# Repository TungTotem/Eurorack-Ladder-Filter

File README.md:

# Eurorack-Ladder-Filter
PCB and EAGLE files for a simple ladder filter I found on the internet. 

Readme

I found this circuit on:
https://note.com/solder_state/n/n598f23105ec4 

Unfortunately it’s all Japanese but we all speak the language of electronics.

Also you might be interested in supporting Hagiwo
https://www.patreon.com/hagiwo
https://www.youtube.com/c/HAGIWO

————————————

This PCB is designed for THT components and side mounted potentiometers so you can squeeze it in a smaller HE blank. All the jacks have to be hardwired.  

I adjusted the 4,7uF film capacitors and used 2,2uF in parallel instead. That reduces hight and also you can get those easier.

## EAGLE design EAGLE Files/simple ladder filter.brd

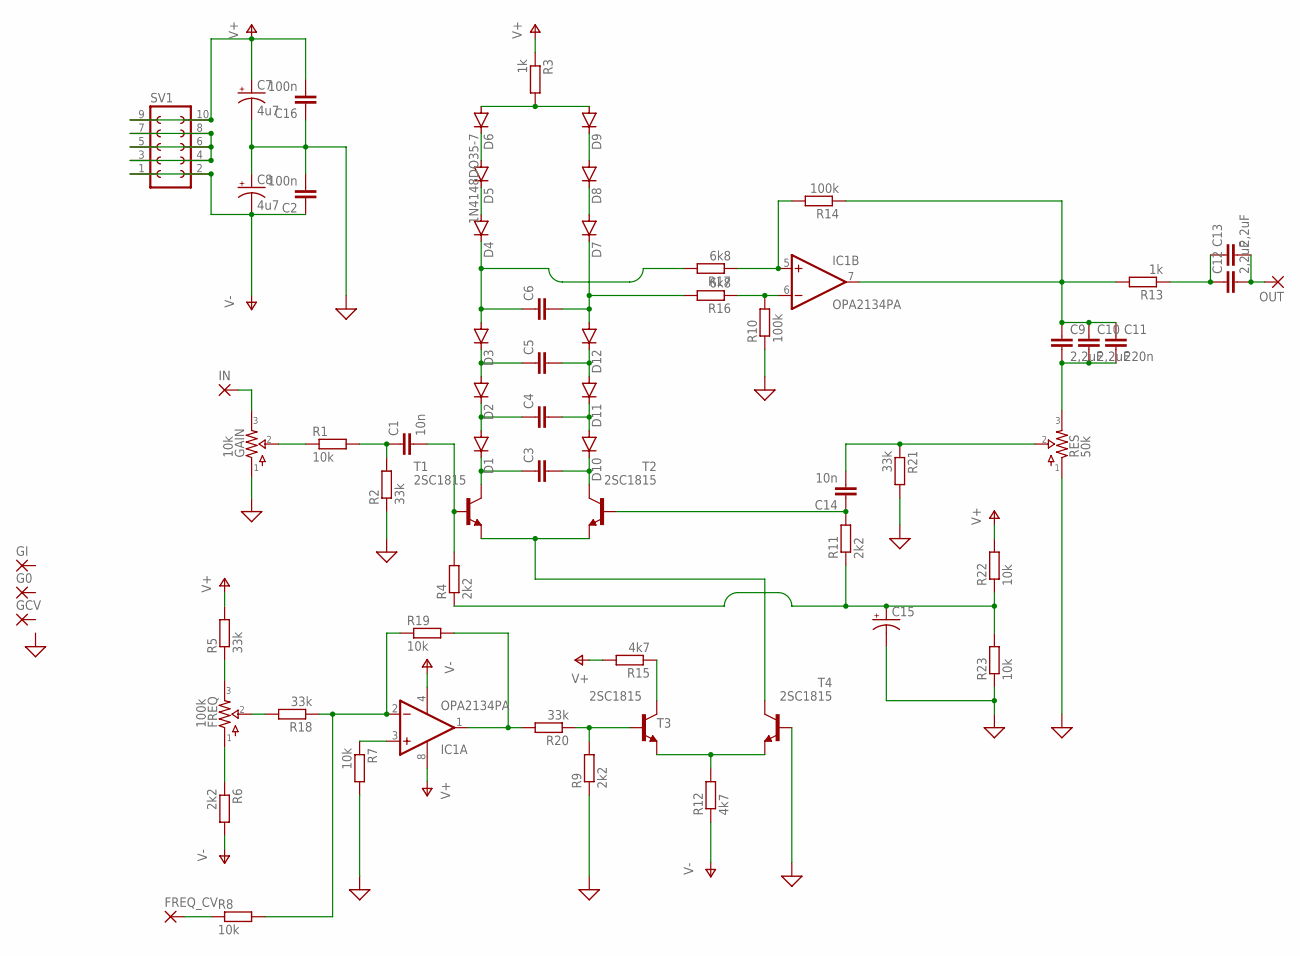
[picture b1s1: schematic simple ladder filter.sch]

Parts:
C1, C14: 10n; C5B3
C2, C16: 100n; C5B3
C3, C4, C5, C6: C2.5/2; C2.5-2
C7, C8: 4u7; E2-4
C9, C10, C12, C13: 2,2uF; C5B5.5
C11: 220n; C5B3
C15: CPOL-USE2-4; E2-4
D1, D2, D3, D4, D5, D6, D7, D8, D9, D10, D11, D12: 1N4148DO35-7; DO35-7
FREQ: 100k; 9MM_VERT
FREQ_CV: 1,6/0,9
G0: 1,6/0,9
GAIN: 10k; 9MM_VERT
GCV: 1,6/0,9
GI: 1,6/0,9
IC1: OPA2134PA; DIL08
IN: 1,6/0,9
OUT: 1,6/0,9
R1, R7, R8, R19, R22, R23: 10k; 0204/7
R2, R5, R18, R20, R21: 33k; 0204/7
R3, R13: 1k; 0204/7
R4, R6, R9, R11: 2k2; 0204/7
R10, R14: 100k; 0204/7
R12, R15: 4k7; 0204/7
R16, R17: 6k8; 0204/7
RES: 50k; 9MM_VERT
SV1: FE05-2
T1, T2, T3, T4: 2SC1815; TO92-ECB

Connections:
GND: C2.2, C7.-, C8.+, C15.-, C16.1, GAIN.1, R2.1, R7.2, R9.1, R10.1, R21.2, R23.1, RES.1, T4.B
unnamed: GAIN.3, IN.1
unnamed: GAIN.2, R1.1
unnamed: C1.1, R1.2, R2.2
unnamed: C1.2, R4.2, T1.B
unnamed: FREQ.3, R5.1
unnamed: FREQ.1, R6.1
unnamed: FREQ.2, R18.2
unnamed: FREQ_CV.1, R8.1
unnamed: IC1.2 (-IN), R8.2, R18.1, R19.1
unnamed: D7.A, D8.C
unnamed: C3.1, D1.C, T1.C
unnamed: C4.1, D1.A, D2.C
unnamed: C5.1, D2.A, D3.C
unnamed: C6.1, D3.A, D4.C, R17.2
unnamed: D4.A, D5.C
unnamed: D5.A, D6.C
unnamed: D8.A, D9.C
unnamed: C6.2, D7.C, D12.A, R16.2
unnamed: C5.2, D11.A, D12.C
unnamed: C4.2, D10.A, D11.C
unnamed: C3.2, D10.C, T2.C
unnamed: D6.A, D9.A, R3.2
unnamed: IC1.3 (+IN), R7.1
unnamed: IC1.1 (OUT), R19.2, R20.2
unnamed: R9.2, R20.1, T3.B
unnamed: R12.2, T3.E, T4.E
unnamed: IC1.6 (-IN), R10.2, R16.1
unnamed: T1.E, T2.E, T4.C
unnamed: R15.1, T3.C
unnamed: IC1.5 (+IN), R14.2, R17.1
unnamed: C15.+, R4.1, R11.1, R22.1, R23.2
unnamed: C12.1, C13.1, R13.1
unnamed: C12.2, C13.2, OUT.1
unnamed: C9.1, C10.1, C11.1, IC1.7 (OUT), R13.2, R14.1
unnamed: C9.2, C10.2, C11.2, RES.3
unnamed: C14.1, R11.2, T2.B
unnamed: C14.2, R21.1, RES.2
unnamed: SV1.3, SV1.4, SV1.5, SV1.6, SV1.7, SV1.8
V+: C7.+, C16.2, IC1.8 (V+), R3.1, R5.2, R15.2, R22.2, SV1.9, SV1.10
V-: C2.1, C8.-, IC1.4 (V-), R6.2, R12.1, SV1.1, SV1.2

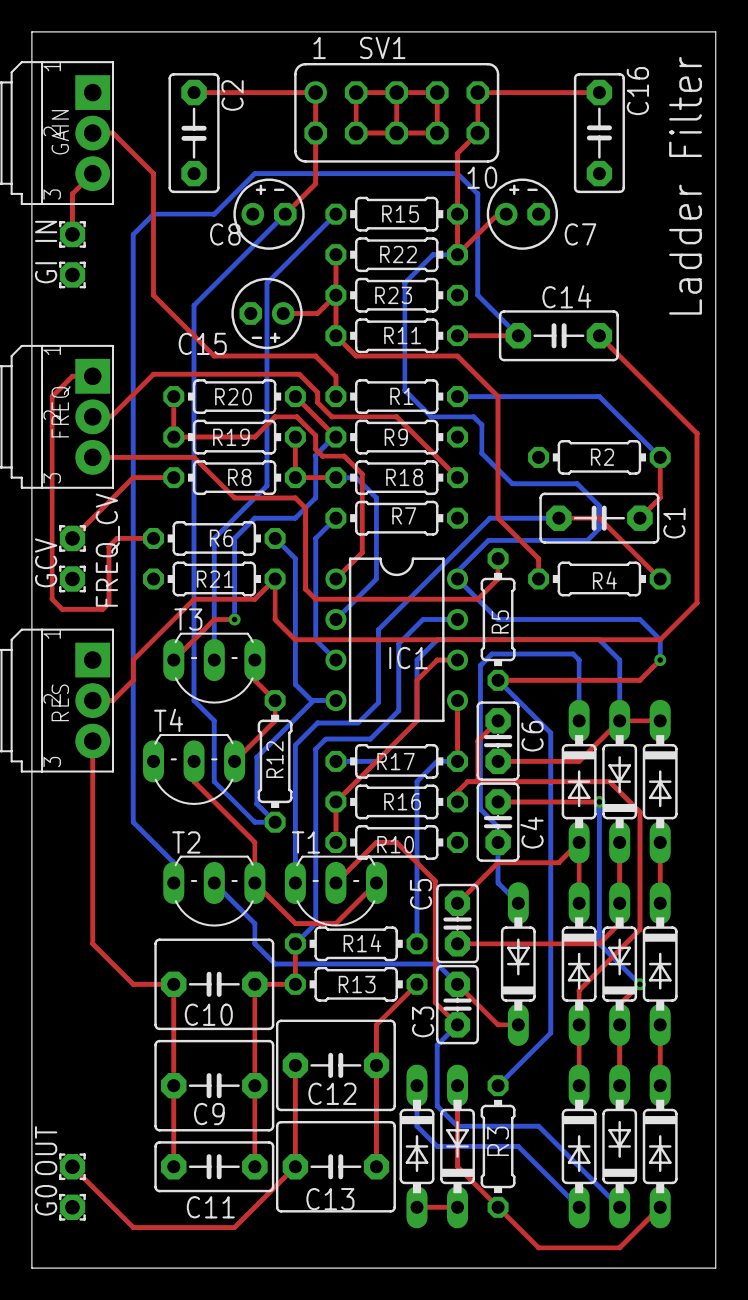
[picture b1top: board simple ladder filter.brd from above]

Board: 2 copper layers, 42.9 x 77.5 mm, 66 parts (0 on the bottom side), 41 nets.

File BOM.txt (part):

Simple ladder filter

Part    Value        Device       Package  Description                          MF MPN OC_FARNELL OC_NEWARK POPULARITY SPICEPREFIX
C1      10n          C5/3         C5B3     CAPACITOR                                                        4                     
C2      100n         C5/3         C5B3     CAPACITOR                                                        4                     
C3                   C2.5/2       C2.5-2   CAPACITOR                                                        28                    
C4                   C2.5/2       C2.5-2   CAPACITOR                                                        28                    
C5                   C2.5/2       C2.5-2   CAPACITOR                                                        28                    
C6                   C2.5/2       C2.5-2   CAPACITOR                                                        28                    
C7      4u7          CPOL-USE2-4  E2-4     POLARIZED CAPACITOR, American symbol                                                   
C8      4u7          CPOL-USE2-4  E2-4     POLARIZED CAPACITOR, American symbol                                                   
C9      2,2uF        C5/5.5       C5B5.5   CAPACITOR                                                        1                     
C10     2,2uF        C5/5.5       C5B5.5   CAPACITOR                                                        1                     
C11     220n         C5/3         C5B3     CAPACITOR                                                        4                     
C12     2,2uF        C5/5.5       C5B5.5   CAPACITOR                                                        1                     
C13     2,2uF        C5/5.5       C5B5.5   CAPACITOR                                                        1                     
C14     10n          C5/3         C5B3     CAPACITOR                                                        4                     
C15                  CPOL-USE2-4  E2-4     POLARIZED CAPACITOR, American symbol                                                   
C16     100n         C5/3         C5B3     CAPACITOR                                                        4                     
D1      1N4148DO35-7 1N4148DO35-7 DO35-7   DIODE                                                            58                    
D2      1N4148DO35-7 1N4148DO35-7 DO35-7   DIODE                                                            58                    
D3      1N4148DO35-7 1N4148DO35-7 DO35-7   DIODE                                                            58                    
D4      1N4148DO35-7 1N4148DO35-7 DO35-7   DIODE                                                            58                    
D5      1N4148DO35-7 1N4148DO35-7 DO35-7   DIODE                                                            58                    
D6      1N4148DO35-7 1N4148DO35-7 DO35-7   DIODE                                                            58                    
D7      1N4148DO35-7 1N4148DO35-7 DO35-7   DIODE                                                            58                    
D8      1N4148DO35-7 1N4148DO35-7 DO35-7   DIODE                                                            58                    
D9      1N4148DO35-7 1N4148DO35-7 DO35-7   DIODE                                                            58                    
D10     1N4148DO35-7 1N4148DO35-7 DO35-7   DIODE                                                            58                    
D11     1N4148DO35-7 1N4148DO35-7 DO35-7   DIODE                                                            58                    
D12     1N4148DO35-7 1N4148DO35-7 DO35-7   DIODE                                                            58                    
FREQ    100k         POTS9MM_VERT 9MM_VERT                                                                                        
FREQ_CV              1,6/0,9      1,6/0,9  THROUGH-HOLE PAD                                                 7                     
G0                   1,6/0,9      1,6/0,9  THROUGH-HOLE PAD                                                 7                     
GAIN    10k          POTS9MM_VERT 9MM_VERT                                                                                        
GCV                  1,6/0,9      1,6/0,9  THROUGH-HOLE PAD                                                 7                     
GI                   1,6/0,9      1,6/0,9  THROUGH-HOLE PAD                                                 7                     
IC1     OPA2134PA    OPA2134PA    DIL08    Dual Operational Amplifier                                       0                     
IN                   1,6/0,9      1,6/0,9  THROUGH-HOLE PAD                                                 7                     
OUT                  1,6/0,9      1,6/0,9  THROUGH-HOLE PAD                                                 7                     
R1      10k          R-EU_0204/7  0204/7   RESISTOR, European symbol                                        79         R          
R2      33k          R-EU_0204/7  0204/7   RESISTOR, European symbol                                        79         R          
R3      1k           R-EU_0204/7  0204/7   RESISTOR, European symbol                                        79         R          
R4      2k2          R-EU_0204/7  0204/7   RESISTOR, European symbol                                        79         R          
R5      33k          R-EU_0204/7  0204/7   RESISTOR, European symbol                                        79         R          
R6      2k2          R-EU_0204/7  0204/7   RESISTOR, European symbol                                        79         R          
R7      10k          R-EU_0204/7  0204/7   RESISTOR, European symbol                                        79         R          
R8      10k          R-EU_0204/7  0204/7   RESISTOR, European symbol                                        79         R          
R9      2k2          R-EU_0204/7  0204/7   RESISTOR, European symbol                                        79         R          
R10     100k         R-EU_0204/7  0204/7   RESISTOR, European symbol                                        79         R          
R11     2k2          R-EU_0204/7  0204/7   RESISTOR, European symbol                                        79         R          
R12     4k7          R-EU_0204/7  0204/7   RESISTOR, European symbol                                        79         R          
R13     1k           R-EU_0204/7  0204/7   RESISTOR, European symbol                                        79         R          
R14     100k         R-EU_0204/7  0204/7   RESISTOR, European symbol                                        79         R          
R15     4k7          R-EU_0204/7  0204/7   RESISTOR, European symbol                                        79         R          
R16     6k8          R-EU_0204/7  0204/7   RESISTOR, European symbol                                        79         R          
R17     6k8          R-EU_0204/7  0204/7   RESISTOR, European symbol                                        79         R          
R18     33k          R-EU_0204/7  0204/7   RESISTOR, European symbol                                        79         R          
R19     10k          R-EU_0204/7  0204/7   RESISTOR, European symbol                                        79         R          
R20     33k          R-EU_0204/7  0204/7   RESISTOR, European symbol                                        79         R          
R21     33k          R-EU_0204/7  0204/7   RESISTOR, European symbol                                        79         R          
R22     10k          R-EU_0204/7  0204/7   RESISTOR, European symbol                                        79         R          
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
